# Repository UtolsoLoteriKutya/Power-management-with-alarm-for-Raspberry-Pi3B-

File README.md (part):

<html xmlns:v="urn:schemas-microsoft-com:vml"
xmlns:o="urn:schemas-microsoft-com:office:office"
xmlns:w="urn:schemas-microsoft-com:office:word"
xmlns:m="http://schemas.microsoft.com/office/2004/12/omml"
xmlns="http://www.w3.org/TR/REC-html40">

<head>
<meta http-equiv=Content-Type content="text/html; charset=windows-1250">
<meta name=ProgId content=Word.Document>
<meta name=Generator content="Microsoft Word 15">
<meta name=Originator content="Microsoft Word 15">
<link rel=File-List href="index_elemei/filelist.xml">
<link rel=Edit-Time-Data href="index_elemei/editdata.mso">
<!--[if !mso]>

<![endif]--><!--[if gte mso 9]><xml>
 <o:DocumentProperties>
  <o:Author>Citrák János</o:Author>
  <o:LastAuthor>Citrák János</o:LastAuthor>
  <o:Revision>5</o:Revision>
  <o:Created>2022-07-11T07:24:00Z</o:Created>
  <o:LastSaved>2022-07-11T10:03:00Z</o:LastSaved>
  <o:Pages>1</o:Pages>
  <o:Words>778</o:Words>
  <o:Characters>4903</o:Characters>
  <o:Lines>40</o:Lines>
  <o:Paragraphs>11</o:Paragraphs>
  <o:CharactersWithSpaces>5670</o:CharactersWithSpaces>
  <o:Version>16.00</o:Version>
 </o:DocumentProperties>
 <o:OfficeDocumentSettings>
  <o:AllowPNG/>
 </o:OfficeDocumentSettings>
</xml><![endif]-->
<link rel=themeData href="index_elemei/themedata.thmx">
<link rel=colorSchemeMapping href="index_elemei/colorschememapping.xml">
<!--[if gte mso 9]><xml>
 <w:WordDocument>
  <w:Zoom>90</w:Zoom>
  <w:TrackMoves>false</w:TrackMoves>
  <w:TrackFormatting/>
  <w:HyphenationZone>21</w:HyphenationZone>
  <w:PunctuationKerning/>
  <w:ValidateAgainstSchemas/>
  <w:SaveIfXMLInvalid>false</w:SaveIfXMLInvalid>
  <w:IgnoreMixedContent>false</w:IgnoreMixedContent>
  <w:AlwaysShowPlaceholderText>false</w:AlwaysShowPlaceholderText>
  <w:DoNotPromoteQF/>
  <w:LidThemeOther>DE</w:LidThemeOther>
  <w:LidThemeAsian>X-NONE</w:LidThemeAsian>
  <w:LidThemeComplexScript>AR-SA</w:LidThemeComplexScript>
  <w:Compatibility>
   <w:BreakWrappedTables/>
   <w:SnapToGridInCell/>
   <w:WrapTextWithPunct/>
   <w:UseAsianBreakRules/>
   <w:DontGrowAutofit/>
   <w:SplitPgBreakAndParaMark/>
   <w:EnableOpenTypeKerning/>
   <w:DontFlipMirrorIndents/>
   <w:OverrideTableStyleHps/>
  </w:Compatibility>
  <m:mathPr>
   <m:mathFont m:val="Cambria Math"/>
   <m:brkBin m:val="before"/>
   <m:brkBinSub m:val="&#45;-"/>
   <m:smallFrac m:val="off"/>
   <m:dispDef/>
   <m:lMargin m:val="0"/>
   <m:rMargin m:val="0"/>
   <m:defJc m:val="centerGroup"/>
   <m:wrapIndent m:val="1440"/>
   <m:intLim m:val="subSup"/>
   <m:naryLim m:val="undOvr"/>
  </m:mathPr></w:WordDocument>
</xml><![endif]--><!--[if gte mso 9]><xml>
 <w:LatentStyles DefLockedState="false" DefUnhideWhenUsed="false"
  DefSemiHidden="false" DefQFormat="false" DefPriority="99"
  LatentStyleCount="376">
  <w:LsdException Locked="false" Priority="0" QFormat="true" Name="Normal"/>
  <w:LsdException Locked="false" Priority="9" QFormat="true" Name="heading 1"/>
  <w:LsdException Locked="false" Priority="9" SemiHidden="true"
   UnhideWhenUsed="true" QFormat="true" Name="heading 2"/>
  <w:LsdException Locked="false" Priority="9" SemiHidden="true"
   UnhideWhenUsed="true" QFormat="true" Name="heading 3"/>
  <w:LsdException Locked="false" Priority="9" SemiHidden="true"
   UnhideWhenUsed="true" QFormat="true" Name="heading 4"/>
  <w:LsdException Locked="false" Priority="9" SemiHidden="true"
   UnhideWhenUsed="true" QFormat="true" Name="heading 5"/>
  <w:LsdException Locked="false" Priority="9" SemiHidden="true"
   UnhideWhenUsed="true" QFormat="true" Name="heading 6"/>
  <w:LsdException Locked="false" Priority="9" SemiHidden="true"
   UnhideWhenUsed="true" QFormat="true" Name="heading 7"/>
  <w:LsdException Locked="false" Priority="9" SemiHidden="true"
   UnhideWhenUsed="true" QFormat="true" Name="heading 8"/>
  <w:LsdException Locked="false" Priority="9" SemiHidden="true"
   UnhideWhenUsed="true" QFormat="true" Name="heading 9"/>
  <w:LsdException Locked="false" SemiHidden="true" UnhideWhenUsed="true"
   Name="index 1"/>
  <w:LsdException Locked="false" SemiHidden="true" UnhideWhenUsed="true"
   Name="index 2"/>
  <w:LsdException Locked="false" SemiHidden="true" UnhideWhenUsed="true"
   Name="index 3"/>
  <w:LsdException Locked="false" SemiHidden="true" UnhideWhenUsed="true"
   Name="index 4"/>
  <w:LsdException Locked="false" SemiHidden="true" UnhideWhenUsed="true"
   Name="index 5"/>
  <w:LsdException Locked="false" SemiHidden="true" UnhideWhenUsed="true"
   Name="index 6"/>
  <w:LsdException Locked="false" SemiHidden="true" UnhideWhenUsed="true"
   Name="index 7"/>
  <w:LsdException Locked="false" SemiHidden="true" UnhideWhenUsed="true"
   Name="index 8"/>
  <w:LsdException Locked="false" SemiHidden="true" UnhideWhenUsed="true"
   Name="index 9"/>
  <w:LsdException Locked="false" Priority="39" SemiHidden="true"
   UnhideWhenUsed="true" Name="toc 1"/>
  <w:LsdException Locked="false" Priority="39" SemiHidden="true"
   UnhideWhenUsed="true" Name="toc 2"/>
  <w:LsdException Locked="false" Priority="39" SemiHidden="true"
   UnhideWhenUsed="true" Name="toc 3"/>
  <w:LsdException Locked="false" Priority="39" SemiHidden="true"
   UnhideWhenUsed="true" Name="toc 4"/>
  <w:LsdException Locked="false" Priority="39" SemiHidden="true"
   UnhideWhenUsed="true" Name="toc 5"/>
  <w:LsdException Locked="false" Priority="39" SemiHidden="true"
   UnhideWhenUsed="true" Name="toc 6"/>
  <w:LsdException Locked="false" Priority="39" SemiHidden="true"
   UnhideWhenUsed="true" Name="toc 7"/>
  <w:LsdException Locked="false" Priority="39" SemiHidden="true"
   UnhideWhenUsed="true" Name="toc 8"/>
  <w:LsdException Locked="false" Priority="39" SemiHidden="true"
   UnhideWhenUsed="true" Name="toc 9"/>
  <w:LsdException Locked="false" SemiHidden="true" UnhideWhenUsed="true"
   Name="Normal Indent"/>
  <w:LsdException Locked="false" SemiHidden="true" UnhideWhenUsed="true"
   Name="footnote text"/>
  <w:LsdException Locked="false" SemiHidden="true" UnhideWhenUsed="true"
   Name="annotation text"/>
  <w:LsdException Locked="false" SemiHidden="true" UnhideWhenUsed="true"
   Name="header"/>
  <w:LsdException Locked="false" SemiHidden="true" UnhideWhenUsed="true"
   Name="footer"/>
  <w:LsdException Locked="false" SemiHidden="true" UnhideWhenUsed="true"
   Name="index heading"/>
  <w:LsdException Locked="false" Priority="35" SemiHidden="true"
   UnhideWhenUsed="true" QFormat="true" Name="caption"/>
  <w:LsdException Locked="false" SemiHidden="true" UnhideWhenUsed="true"
   Name="table of figures"/>
  <w:LsdException Locked="false" SemiHidden="true" UnhideWhenUsed="true"
   Name="envelope address"/>
  <w:LsdException Locked="false" SemiHidden="true" UnhideWhenUsed="true"
   Name="envelope return"/>
  <w:LsdException Locked="false" SemiHidden="true" UnhideWhenUsed="true"
   Name="footnote reference"/>
  <w:LsdException Locked="false" SemiHidden="true" UnhideWhenUsed="true"
   Name="annotation reference"/>
  <w:LsdException Locked="false" SemiHidden="true" UnhideWhenUsed="true"
   Name="line number"/>
  <w:LsdException Locked="false" SemiHidden="true" UnhideWhenUsed="true"
   Name="page number"/>
  <w:LsdException Locked="false" SemiHidden="true" UnhideWhenUsed="true"
   Name="endnote reference"/>
  <w:LsdException Locked="false" SemiHidden="true" UnhideWhenUsed="true"
   Name="endnote text"/>
  <w:LsdException Locked="false" SemiHidden="true" UnhideWhenUsed="true"
   Name="table of authorities"/>
  <w:LsdException Locked="false" SemiHidden="true" UnhideWhenUsed="true"
   Name="macro"/>
  <w:LsdException Locked="false" SemiHidden="true" UnhideWhenUsed="true"
   Name="toa heading"/>
  <w:LsdException Locked="false" SemiHidden="true" UnhideWhenUsed="true"
   Name="List"/>
  <w:LsdException Locked="false" SemiHidden="true" UnhideWhenUsed="true"
   Name="List Bullet"/>
  <w:LsdException Locked="false" SemiHidden="true" UnhideWhenUsed="true"
   Name="List Number"/>
  <w:LsdException Locked="false" SemiHidden="true" UnhideWhenUsed="true"
   Name="List 2"/>
  <w:LsdException Locked="false" SemiHidden="true" UnhideWhenUsed="true"
   Name="List 3"/>
  <w:LsdException Locked="false" SemiHidden="true" UnhideWhenUsed="true"
   Name="List 4"/>
  <w:LsdException Locked="false" SemiHidden="true" UnhideWhenUsed="true"
   Name="List 5"/>
  <w:LsdException Locked="false" SemiHidden="true" UnhideWhenUsed="true"
   Name="List Bullet 2"/>
  <w:LsdException Locked="false" SemiHidden="true" UnhideWhenUsed="true"
   Name="List Bullet 3"/>
  <w:LsdException Locked="false" SemiHidden="true" UnhideWhenUsed="true"
   Name="List Bullet 4"/>
  <w:LsdException Locked="false" SemiHidden="true" UnhideWhenUsed="true"
   Name="List Bullet 5"/>
  <w:LsdException Locked="false" SemiHidden="true" UnhideWhenUsed="true"
   Name="List Number 2"/>
  <w:LsdException Locked="false" SemiHidden="true" UnhideWhenUsed="true"
   Name="List Number 3"/>
  <w:LsdException Locked="false" SemiHidden="true" UnhideWhenUsed="true"
   Name="List Number 4"/>
  <w:LsdException Locked="false" SemiHidden="true" UnhideWhenUsed="true"
   Name="List Number 5"/>
  <w:LsdException Locked="false" Priority="10" QFormat="true" Name="Title"/>
  <w:LsdException Locked="false" SemiHidden="true" UnhideWhenUsed="true"
   Name="Closing"/>
  <w:LsdException Locked="false" SemiHidden="true" UnhideWhenUsed="true"
   Name="Signature"/>
  <w:LsdException Locked="false" Priority="1" SemiHidden="true"
   UnhideWhenUsed="true" Name="Default Paragraph Font"/>
  <w:LsdException Locked="false" SemiHidden="true" UnhideWhenUsed="true"
   Name="Body Text"/>
  <w:LsdException Locked="false" SemiHidden="true" UnhideWhenUsed="true"
   Name="Body Text Indent"/>
  <w:LsdException Locked="false" SemiHidden="true" UnhideWhenUsed="true"
   Name="List Continue"/>
  <w:LsdException Locked="false" SemiHidden="true" UnhideWhenUsed="true"
   Name="List Continue 2"/>
  <w:LsdException Locked="false" SemiHidden="true" UnhideWhenUsed="true"
   Name="List Continue 3"/>
  <w:LsdException Locked="false" SemiHidden="true" UnhideWhenUsed="true"
   Name="List Continue 4"/>
  <w:LsdException Locked="false" SemiHidden="true" UnhideWhenUsed="true"
   Name="List Continue 5"/>
  <w:LsdException Locked="false" SemiHidden="true" UnhideWhenUsed="true"
   Name="Message Header"/>
  <w:LsdException Locked="false" Priority="11" QFormat="true" Name="Subtitle"/>
  <w:LsdException Locked="false" SemiHidden="true" UnhideWhenUsed="true"
   Name="Salutation"/>
  <w:LsdException Locked="false" SemiHidden="true" UnhideWhenUsed="true"
   Name="Date"/>
  <w:LsdException Locked="false" SemiHidden="true" UnhideWhenUsed="true"
   Name="Body Text First Indent"/>
  <w:LsdException Locked="false" SemiHidden="true" UnhideWhenUsed="true"
   Name="Body Text First Indent 2"/>
  <w:LsdException Locked="false" SemiHidden="true" UnhideWhenUsed="true"
   Name="Note Heading"/>
  <w:LsdException Locked="false" SemiHidden="true" UnhideWhenUsed="true"
   Name="Body Text 2"/>
  <w:LsdException Locked="false" SemiHidden="true" UnhideWhenUsed="true"
   Name="Body Text 3"/>
  <w:LsdException Locked="false" SemiHidden="true" UnhideWhenUsed="true"
   Name="Body Text Indent 2"/>
  <w:LsdException Locked="false" SemiHidden="true" UnhideWhenUsed="true"
   Name="Body Text Indent 3"/>
  <w:LsdException Locked="false" SemiHidden="true" UnhideWhenUsed="true"
   Name="Block Text"/>
  <w:LsdException Locked="false" SemiHidden="true" UnhideWhenUsed="true"
   Name="Hyperlink"/>
  <w:LsdException Locked="false" SemiHidden="true" UnhideWhenUsed="true"
   Name="FollowedHyperlink"/>
  <w:LsdException Locked="false" Priority="22" QFormat="true" Name="Strong"/>
  <w:LsdException Locked="false" Priority="20" QFormat="true" Name="Emphasis"/>
  <w:LsdException Locked="false" SemiHidden="true" UnhideWhenUsed="true"
   Name="Document Map"/>
  <w:LsdException Locked="false" SemiHidden="true" UnhideWhenUsed="true"
   Name="Plain Text"/>
  <w:LsdException Locked="false" SemiHidden="true" UnhideWhenUsed="true"
   Name="E-mail Signature"/>
  <w:LsdException Locked="false" SemiHidden="true" UnhideWhenUsed="true"
   Name="HTML Top of Form"/>
  <w:LsdException Locked="false" SemiHidden="true" UnhideWhenUsed="true"
   Name="HTML Bottom of Form"/>
  <w:LsdException Locked="false" SemiHidden="true" UnhideWhenUsed="true"
   Name="Normal (Web)"/>
  <w:LsdException Locked="false" SemiHidden="true" UnhideWhenUsed="true"
   Name="HTML Acronym"/>
  <w:LsdException Locked="false" SemiHidden="true" UnhideWhenUsed="true"
   Name="HTML Address"/>
  <w:LsdException Locked="false" SemiHidden="true" UnhideWhenUsed="true"
   Name="HTML Cite"/>
  <w:LsdException Locked="false" SemiHidden="true" UnhideWhenUsed="true"
   Name="HTML Code"/>
  <w:LsdException Locked="false" SemiHidden="true" UnhideWhenUsed="true"
   Name="HTML Definition"/>
  <w:LsdException Locked="false" SemiHidden="true" UnhideWhenUsed="true"
   Name="HTML Keyboard"/>
  <w:LsdException Locked="false" SemiHidden="true" UnhideWhenUsed="true"
   Name="HTML Preformatted"/>
  <w:LsdException Locked="false" SemiHidden="true" UnhideWhenUsed="true"
   Name="HTML Sample"/>
  <w:LsdException Locked="false" SemiHidden="true" UnhideWhenUsed="true"
   Name="HTML Typewriter"/>
  <w:LsdException Locked="false" SemiHidden="true" UnhideWhenUsed="true"
   Name="HTML Variable"/>
  <w:LsdException Locked="false" SemiHidden="true" UnhideWhenUsed="true"
   Name="Normal Table"/>
  <w:LsdException Locked="false" SemiHidden="true" UnhideWhenUsed="true"
   Name="annotation subject"/>
  <w:LsdException Locked="false" SemiHidden="true" UnhideWhenUsed="true"
   Name="No List"/>
  <w:LsdException Locked="false" SemiHidden="true" UnhideWhenUsed="true"
   Name="Outline List 1"/>
  <w:LsdException Locked="false" SemiHidden="true" UnhideWhenUsed="true"
   Name="Outline List 2"/>
  <w:LsdException Locked="false" SemiHidden="true" UnhideWhenUsed="true"
   Name="Outline List 3"/>
  <w:LsdException Locked="false" SemiHidden="true" UnhideWhenUsed="true"
   Name="Table Simple 1"/>
  <w:LsdException Locked="false" SemiHidden="true" UnhideWhenUsed="true"
   Name="Table Simple 2"/>
  <w:LsdException Locked="false" SemiHidden="true" UnhideWhenUsed="true"
   Name="Table Simple 3"/>
  <w:LsdException Locked="false" SemiHidden="true" UnhideWhenUsed="true"
   Name="Table Classic 1"/>
  <w:LsdException Locked="false" SemiHidden="true" UnhideWhenUsed="true"
   Name="Table Classic 2"/>
  <w:LsdException Locked="false" SemiHidden="true" UnhideWhenUsed="true"
   Name="Table Classic 3"/>
  <w:LsdException Locked="false" SemiHidden="true" UnhideWhenUsed="true"
   Name="Table Classic 4"/>
  <w:LsdException Locked="false" SemiHidden="true" UnhideWhenUsed="true"
   Name="Table Colorful 1"/>
  <w:LsdException Locked="false" SemiHidden="true" UnhideWhenUsed="true"
   Name="Table Colorful 2"/>
  <w:LsdException Locked="false" SemiHidden="true" UnhideWhenUsed="true"
   Name="Table Colorful 3"/>
  <w:LsdException Locked="false" SemiHidden="true" UnhideWhenUsed="true"
   Name="Table Columns 1"/>
  <w:LsdException Locked="false" SemiHidden="true" UnhideWhenUsed="true"
   Name="Table Columns 2"/>
  <w:LsdException Locked="false" SemiHidden="true" UnhideWhenUsed="true"
   Name="Table Columns 3"/>
  <w:LsdException Locked="false" SemiHidden="true" UnhideWhenUsed="true"
   Name="Table Columns 4"/>
  <w:LsdException Locked="false" SemiHidden="true" UnhideWhenUsed="true"
   Name="Table Columns 5"/>
  <w:LsdException Locked="false" SemiHidden="true" UnhideWhenUsed="true"
   Name="Table Grid 1"/>
  <w:LsdException Locked="false" SemiHidden="true" UnhideWhenUsed="true"
   Name="Table Grid 2"/>
  <w:LsdException Locked="false" SemiHidden="true" UnhideWhenUsed="true"
   Name="Table Grid 3"/>
  <w:LsdException Locked="false" SemiHidden="true" UnhideWhenUsed="true"
   Name="Table Grid 4"/>
  <w:LsdException Locked="false" SemiHidden="true" UnhideWhenUsed="true"
   Name="Table Grid 5"/>
  <w:LsdException Locked="false" SemiHidden="true" UnhideWhenUsed="true"
   Name="Table Grid 6"/>
  <w:LsdException Locked="false" SemiHidden="true" UnhideWhenUsed="true"
   Name="Table Grid 7"/>
  <w:LsdException Locked="false" SemiHidden="true" UnhideWhenUsed="true"
   Name="Table Grid 8"/>
  <w:LsdException Locked="false" SemiHidden="true" UnhideWhenUsed="true"
   Name="Table List 1"/>
  <w:LsdException Locked="false" SemiHidden="true" UnhideWhenUsed="true"
   Name="Table List 2"/>
  <w:LsdException Locked="false" SemiHidden="true" UnhideWhenUsed="true"
   Name="Table List 3"/>
  <w:LsdException Locked="false" SemiHidden="true" UnhideWhenUsed="true"
   Name="Table List 4"/>
  <w:LsdException Locked="false" SemiHidden="true" UnhideWhenUsed="true"
   Name="Table List 5"/>
  <w:LsdException Locked="false" SemiHidden="true" UnhideWhenUsed="true"
   Name="Table List 6"/>
  <w:LsdException Locked="false" SemiHidden="true" UnhideWhenUsed="true"
   Name="Table List 7"/>
  <w:LsdException Locked="false" SemiHidden="true" UnhideWhenUsed="true"
   Name="Table List 8"/>
  <w:LsdException Locked="false" SemiHidden="true" UnhideWhenUsed="true"
   Name="Table 3D effects 1"/>
  <w:LsdException Locked="false" SemiHidden="true" UnhideWhenUsed="true"
   Name="Table 3D effects 2"/>
  <w:LsdException Locked="false" SemiHidden="true" UnhideWhenUsed="true"
   Name="Table 3D effects 3"/>
  <w:LsdException Locked="false" SemiHidden="true" UnhideWhenUsed="true"
   Name="Table Contemporary"/>
  <w:LsdException Locked="false" SemiHidden="true" UnhideWhenUsed="true"
   Name="Table Elegant"/>
  <w:LsdException Locked="false" SemiHidden="true" UnhideWhenUsed="true"
   Name="Table Professional"/>
  <w:LsdException Locked="false" SemiHidden="true" UnhideWhenUsed="true"
   Name="Table Subtle 1"/>
  <w:LsdException Locked="false" SemiHidden="true" UnhideWhenUsed="true"
   Name="Table Subtle 2"/>
  <w:LsdException Locked="false" SemiHidden="true" UnhideWhenUsed="true"
   Name="Table Web 1"/>
  <w:LsdException Locked="false" SemiHidden="true" UnhideWhenUsed="true"
   Name="Table Web 2"/>
  <w:LsdException Locked="false" SemiHidden="true" UnhideWhenUsed="true"
   Name="Table Web 3"/>
  <w:LsdException Locked="false" SemiHidden="true" UnhideWhenUsed="true"
   Name="Balloon Text"/>
  <w:LsdException Locked="false" Priority="39" Name="Table Grid"/>
  <w:LsdException Locked="false" SemiHidden="true" UnhideWhenUsed="true"
   Name="Table Theme"/>
  <w:LsdException Locked="false" SemiHidden="true" Name="Placeholder Text"/>
  <w:LsdException Locked="false" Priority="1" QFormat="true" Name="No Spacing"/>
  <w:LsdException Locked="false" Priority="60" Name="Light Shading"/>
  <w:LsdException Locked="false" Priority="61" Name="Light List"/>
  <w:LsdException Locked="false" Priority="62" Name="Light Grid"/>
  <w:LsdException Locked="false" Priority="63" Name="Medium Shading 1"/>
  <w:LsdException Locked="false" Priority="64" Name="Medium Shading 2"/>
  <w:LsdException Locked="false" Priority="65" Name="Medium List 1"/>
  <w:LsdException Locked="false" Priority="66" Name="Medium List 2"/>
  <w:LsdException Locked="false" Priority="67" Name="Medium Grid 1"/>
  <w:LsdException Locked="false" Priority="68" Name="Medium Grid 2"/>
  <w:LsdException Locked="false" Priority="69" Name="Medium Grid 3"/>
  <w:LsdException Locked="false" Priority="70" Name="Dark List"/>
  <w:LsdException Locked="false" Priority="71" Name="Colorful Shading"/>
  <w:LsdException Locked="false" Priority="72" Name="Colorful List"/>
  <w:LsdException Locked="false" Priority="73" Name="Colorful Grid"/>
  <w:LsdException Locked="false" Priority="60" Name="Light Shading Accent 1"/>
  <w:LsdException Locked="false" Priority="61" Name="Light List Accent 1"/>
  <w:LsdException Locked="false" Priority="62" Name="Light Grid Accent 1"/>
  <w:LsdException Locked="false" Priority="63" Name="Medium Shading 1 Accent 1"/>
  <w:LsdException Locked="false" Priority="64" Name="Medium Shading 2 Accent 1"/>
  <w:LsdException Locked="false" Priority="65" Name="Medium List 1 Accent 1"/>
  <w:LsdException Locked="false" SemiHidden="true" Name="Revision"/>
  <w:LsdException Locked="false" Priority="34" QFormat="true"
   Name="List Paragraph"/>
  <w:LsdException Locked="false" Priority="29" QFormat="true" Name="Quote"/>
  <w:LsdException Locked="false" Priority="30" QFormat="true"
   Name="Intense Quote"/>
  <w:LsdException Locked="false" Priority="66" Name="Medium List 2 Accent 1"/>
  <w:LsdException Locked="false" Priority="67" Name="Medium Grid 1 Accent 1"/>
  <w:LsdException Locked="false" Priority="68" Name="Medium Grid 2 Accent 1"/>
  <w:LsdException Locked="false" Priority="69" Name="Medium Grid 3 Accent 1"/>
  <w:LsdException Locked="false" Priority="70" Name="Dark List Accent 1"/>
  <w:LsdException Locked="false" Priority="71" Name="Colorful Shading Accent 1"/>
  <w:LsdException Locked="false" Priority="72" Name="Colorful List Accent 1"/>
  <w:LsdException Locked="false" Priority="73" Name="Colorful Grid Accent 1"/>
  <w:LsdException Locked="false" Priority="60" Name="Light Shading Accent 2"/>
  <w:LsdException Locked="false" Priority="61" Name="Light List Accent 2"/>
  <w:LsdException Locked="false" Priority="62" Name="Light Grid Accent 2"/>
  <w:LsdException Locked="false" Priority="63" Name="Medium Shading 1 Accent 2"/>
  <w:LsdException Locked="false" Priority="64" Name="Medium Shading 2 Accent 2"/>
  <w:LsdException Locked="false" Priority="65" Name="Medium List 1 Accent 2"/>
  <w:LsdException Locked="false" Priority="66" Name="Medium List 2 Accent 2"/>
  <w:LsdException Locked="false" Priority="67" Name="Medium Grid 1 Accent 2"/>
  <w:LsdException Locked="false" Priority="68" Name="Medium Grid 2 Accent 2"/>
  <w:LsdException Locked="false" Priority="69" Name="Medium Grid 3 Accent 2"/>
  <w:LsdException Locked="false" Priority="70" Name="Dark List Accent 2"/>
  <w:LsdException Locked="false" Priority="71" Name="Colorful Shading Accent 2"/>
  <w:LsdException Locked="false" Priority="72" Name="Colorful List Accent 2"/>
  <w:LsdException Locked="false" Priority="73" Name="Colorful Grid Accent 2"/>
  <w:LsdException Locked="false" Priority="60" Name="Light Shading Accent 3"/>
  <w:LsdException Locked="false" Priority="61" Name="Light List Accent 3"/>
  <w:LsdException Locked="false" Priority="62" Name="Light Grid Accent 3"/>
  <w:LsdException Locked="false" Priority="63" Name="Medium Shading 1 Accent 3"/>
  <w:LsdException Locked="false" Priority="64" Name="Medium Shading 2 Accent 3"/>
  <w:LsdException Locked="false" Priority="65" Name="Medium List 1 Accent 3"/>
  <w:LsdException Locked="false" Priority="66" Name="Medium List 2 Accent 3"/>
  <w:LsdException Locked="false" Priority="67" Name="Medium Grid 1 Accent 3"/>
  <w:LsdException Locked="false" Priority="68" Name="Medium Grid 2 Accent 3"/>
  <w:LsdException Locked="false" Priority="69" Name="Medium Grid 3 Accent 3"/>
  <w:LsdException Locked="false" Priority="70" Name="Dark List Accent 3"/>
  <w:LsdException Locked="false" Priority="71" Name="Colorful Shading Accent 3"/>
  <w:LsdException Locked="false" Priority="72" Name="Colorful List Accent 3"/>
  <w:LsdException Locked="false" Priority="73" Name="Colorful Grid Accent 3"/>
  <w:LsdException Locked="false" Priority="60" Name="Light Shading Accent 4"/>
  <w:LsdException Locked="false" Priority="61" Name="Light List Accent 4"/>
  <w:LsdException Locked="false" Priority="62" Name="Light Grid Accent 4"/>
  <w:LsdException Locked="false" Priority="63" Name="Medium Shading 1 Accent 4"/>
  <w:LsdException Locked="false" Priority="64" Name="Medium Shading 2 Accent 4"/>
  <w:LsdException Locked="false" Priority="65" Name="Medium List 1 Accent 4"/>
  <w:LsdException Locked="false" Priority="66" Name="Medium List 2 Accent 4"/>
  <w:LsdException Locked="false" Priority="67" Name="Medium Grid 1 Accent 4"/>
  <w:LsdException Locked="false" Priority="68" Name="Medium Grid 2 Accent 4"/>
  <w:LsdException Locked="false" Priority="69" Name="Medium Grid 3 Accent 4"/>
  <w:LsdException Locked="false" Priority="70" Name="Dark List Accent 4"/>
  <w:LsdException Locked="false" Priority="71" Name="Colorful Shading Accent 4"/>
  <w:LsdException Locked="false" Priority="72" Name="Colorful List Accent 4"/>
  <w:LsdException Locked="false" Priority="73" Name="Colorful Grid Accent 4"/>
  <w:LsdException Locked="false" Priority="60" Name="Light Shading Accent 5"/>
  <w:LsdException Locked="false" Priority="61" Name="Light List Accent 5"/>
  <w:LsdException Locked="false" Priority="62" Name="Light Grid Accent 5"/>
  <w:LsdException Locked="false" Priority="63" Name="Medium Shading 1 Accent 5"/>
  <w:LsdException Locked="false" Priority="64" Name="Medium Shading 2 Accent 5"/>
  <w:LsdException Locked="false" Priority="65" Name="Medium List 1 Accent 5"/>
  <w:LsdException Locked="false" Priority="66" Name="Medium List 2 Accent 5"/>
  <w:LsdException Locked="false" Priority="67" Name="Medium Grid 1 Accent 5"/>
  <w:LsdException Locked="false" Priority="68" Name="Medium Grid 2 Accent 5"/>
  <w:LsdException Locked="false" Priority="69" Name="Medium Grid 3 Accent 5"/>
  <w:LsdException Locked="false" Priority="70" Name="Dark List Accent 5"/>
  <w:LsdException Locked="false" Priority="71" Name="Colorful Shading Accent 5"/>
  <w:LsdException Locked="false" Priority="72" Name="Colorful List Accent 5"/>
  <w:LsdException Locked="false" Priority="73" Name="Colorful Grid Accent 5"/>
  <w:LsdException Locked="false" Priority="60" Name="Light Shading Accent 6"/>
  <w:LsdException Locked="false" Priority="61" Name="Light List Accent 6"/>
  <w:LsdException Locked="false" Priority="62" Name="Light Grid Accent 6"/>
  <w:LsdException Locked="false" Priority="63" Name="Medium Shading 1 Accent 6"/>
  <w:LsdException Locked="false" Priority="64" Name="Medium Shading 2 Accent 6"/>
  <w:LsdException Locked="false" Priority="65" Name="Medium List 1 Accent 6"/>
  <w:LsdException Locked="false" Priority="66" Name="Medium List 2 Accent 6"/>
  <w:LsdException Locked="false" Priority="67" Name="Medium Grid 1 Accent 6"/>
  <w:LsdException Locked="false" Priority="68" Name="Medium Grid 2 Accent 6"/>
  <w:LsdException Locked="false" Priority="69" Name="Medium Grid 3 Accent 6"/>
  <w:LsdException Locked="false" Priority="70" Name="Dark List Accent 6"/>
  <w:LsdException Locked="false" Priority="71" Name="Colorful Shading Accent 6"/>
  <w:LsdException Locked="false" Priority="72" Name="Colorful List Accent 6"/>
  <w:LsdException Locked="false" Priority="73" Name="Colorful Grid Accent 6"/>
  <w:LsdException Locked="false" Priority="19" QFormat="true"
   Name="Subtle Emphasis"/>
  <w:LsdException Locked="false" Priority="21" QFormat="true"
   Name="Intense Emphasis"/>
  <w:LsdException Locked="false" Priority="31" QFormat="true"
   Name="Subtle Reference"/>
  <w:LsdException Locked="false" Priority="32" QFormat="true"
   Name="Intense Reference"/>
  <w:LsdException Locked="false" Priority="33" QFormat="true" Name="Book Title"/>
  <w:LsdException Locked="false" Priority="37" SemiHidden="true"
   UnhideWhenUsed="true" Name="Bibliography"/>
  <w:LsdException Locked="false" Priority="39" SemiHidden="true"
   UnhideWhenUsed="true" QFormat="true" Name="TOC Heading"/>
  <w:LsdException Locked="false" Priority="41" Name="Plain Table 1"/>
  <w:LsdException Locked="false" Priority="42" Name="Plain Table 2"/>
  <w:LsdException Locked="false" Priority="43" Name="Plain Table 3"/>
  <w:LsdException Locked="false" Priority="44" Name="Plain Table 4"/>
  <w:LsdException Locked="false" Priority="45" Name="Plain Table 5"/>
  <w:LsdException Locked="false" Priority="40" Name="Grid Table Light"/>
  <w:LsdException Locked="false" Priority="46" Name="Grid Table 1 Light"/>
  <w:LsdException Locked="false" Priority="47" Name="Grid Table 2"/>
  <w:LsdException Locked="false" Priority="48" Name="Grid Table 3"/>
  <w:LsdException Locked="false" Priority="49" Name="Grid Table 4"/>
  <w:LsdException Locked="false" Priority="50" Name="Grid Table 5 Dark"/>
  <w:LsdException Locked="false" Priority="51" Name="Grid Table 6 Colorful"/>
  <w:LsdException Locked="false" Priority="52" Name="Grid Table 7 Colorful"/>
  <w:LsdException Locked="false" Priority="46"
   Name="Grid Table 1 Light Accent 1"/>
  <w:LsdException Locked="false" Priority="47" Name="Grid Table 2 Accent 1"/>
  <w:LsdException Locked="false" Priority="48" Name="Grid Table 3 Accent 1"/>
  <w:LsdException Locked="false" Priority="49" Name="Grid Table 4 Accent 1"/>
  <w:LsdException Locked="false" Priority="50" Name="Grid Table 5 Dark Accent 1"/>
  <w:LsdException Locked="false" Priority="51"
   Name="Grid Table 6 Colorful Accent 1"/>
  <w:LsdException Locked="false" Priority="52"
   Name="Grid Table 7 Colorful Accent 1"/>
  <w:LsdException Locked="false" Priority="46"
   Name="Grid Table 1 Light Accent 2"/>
  <w:LsdException Locked="false" Priority="47" Name="Grid Table 2 Accent 2"/>
  <w:LsdException Locked="false" Priority="48" Name="Grid Table 3 Accent 2"/>
  <w:LsdException Locked="false" Priority="49" Name="Grid Table 4 Accent 2"/>
  <w:LsdException Locked="false" Priority="50" Name="Grid Table 5 Dark Accent 2"/>
  <w:LsdException Locked="false" Priority="51"
   Name="Grid Table 6 Colorful Accent 2"/>
  <w:LsdException Locked="false" Priority="52"
   Name="Grid Table 7 Colorful Accent 2"/>
  <w:LsdException Locked="false" Priority="46"
   Name="Grid Table 1 Light Accent 3"/>
  <w:LsdException Locked="false" Priority="47" Name="Grid Table 2 Accent 3"/>
  <w:LsdException Locked="false" Priority="48" Name="Grid Table 3 Accent 3"/>
  <w:LsdException Locked="false" Priority="49" Name="Grid Table 4 Accent 3"/>
  <w:LsdException Locked="false" Priority="50" Name="Grid Table 5 Dark Accent 3"/>
  <w:LsdException Locked="false" Priority="51"
   Name="Grid Table 6 Colorful Accent 3"/>
  <w:LsdException Locked="false" Priority="52"
   Name="Grid Table 7 Colorful Accent 3"/>
  <w:LsdException Locked="false" Priority="46"
   Name="Grid Table 1 Light Accent 4"/>
  <w:LsdException Locked="false" Priority="47" Name="Grid Table 2 Accent 4"/>
  <w:LsdException Locked="false" Priority="48" Name="Grid Table 3 Accent 4"/>
  <w:LsdException Locked="false" Priority="49" Name="Grid Table 4 Accent 4"/>
  <w:LsdException Locked="false" Priority="50" Name="Grid Table 5 Dark Accent 4"/>
  <w:LsdException Locked="false" Priority="51"
   Name="Grid Table 6 Colorful Accent 4"/>
  <w:LsdException Locked="false" Priority="52"
   Name="Grid Table 7 Colorful Accent 4"/>
  <w:LsdException Locked="false" Priority="46"
   Name="Grid Table 1 Light Accent 5"/>
  <w:LsdException Locked="false" Priority="47" Name="Grid Table 2 Accent 5"/>
  <w:LsdException Locked="false" Priority="48" Name="Grid Table 3 Accent 5"/>
  <w:LsdException Locked="false" Priority="49" Name="Grid Table 4 Accent 5"/>
  <w:LsdException Locked="false" Priority="50" Name="Grid Table 5 Dark Accent 5"/>
  <w:LsdException Locked="false" Priority="51"
   Name="Grid Table 6 Colorful Accent 5"/>
  <w:LsdException Locked="false" Priority="52"
   Name="Grid Table 7 Colorful Accent 5"/>
  <w:LsdException Locked="false" Priority="46"
   Name="Grid Table 1 Light Accent 6"/>
  <w:LsdException Locked="false" Priority="47" Name="Grid Table 2 Accent 6"/>
  <w:LsdException Locked="false" Priority="48" Name="Grid Table 3 Accent 6"/>
  <w:LsdException Locked="false" Priority="49" Name="Grid Table 4 Accent 6"/>
  <w:LsdException Locked="false" Priority="50" Name="Grid Table 5 Dark Accent 6"/>
  <w:LsdException Locked="false" Priority="51"
   Name="Grid Table 6 Colorful Accent 6"/>
  <w:LsdException Locked="false" Priority="52"
   Name="Grid Table 7 Colorful Accent 6"/>
  <w:LsdException Locked="false" Priority="46" Name="List Table 1 Light"/>
  <w:LsdException Locked="false" Priority="47" Name="List Table 2"/>
  <w:LsdException Locked="false" Priority="48" Name="List Table 3"/>
  <w:LsdException Locked="false" Priority="49" Name="List Table 4"/>
  <w:LsdException Locked="false" Priority="50" Name="List Table 5 Dark"/>
  <w:LsdException Locked="false" Priority="51" Name="List Table 6 Colorful"/>
  <w:LsdException Locked="false" Priority="52" Name="List Table 7 Colorful"/>
  <w:LsdException Locked="false" Priority="46"
   Name="List Table 1 Light Accent 1"/>
  <w:LsdException Locked="false" Priority="47" Name="List Table 2 Accent 1"/>
  <w:LsdException Locked="false" Priority="48" Name="List Table 3 Accent 1"/>
  <w:LsdException Locked="false" Priority="49" Name="List Table 4 Accent 1"/>
  <w:LsdException Locked="false" Priority="50" Name="List Table 5 Dark Accent 1"/>
  <w:LsdException Locked="false" Priority="51"
   Name="List Table 6 Colorful Accent 1"/>
  <w:LsdException Locked="false" Priority="52"
   Name="List Table 7 Colorful Accent 1"/>
  <w:LsdException Locked="false" Priority="46"
   Name="List Table 1 Light Accent 2"/>
  <w:LsdException Locked="false" Priority="47" Name="List Table 2 Accent 2"/>
  <w:LsdException Locked="false" Priority="48" Name="List Table 3 Accent 2"/>
  <w:LsdException Locked="false" Priority="49" Name="List Table 4 Accent 2"/>
  <w:LsdException Locked="false" Priority="50" Name="List Table 5 Dark Accent 2"/>
  <w:LsdException Locked="false" Priority="51"
   Name="List Table 6 Colorful Accent 2"/>
  <w:LsdException Locked="false" Priority="52"
   Name="List Table 7 Colorful Accent 2"/>
  <w:LsdException Locked="false" Priority="46"
   Name="List Table 1 Light Accent 3"/>
  <w:LsdException Locked="false" Priority="47" Name="List Table 2 Accent 3"/>
  <w:LsdException Locked="false" Priority="48" Name="List Table 3 Accent 3"/>
  <w:LsdException Locked="false" Priority="49" Name="List Table 4 Accent 3"/>
  <w:LsdException Locked="false" Priority="50" Name="List Table 5 Dark Accent 3"/>
  <w:LsdException Locked="false" Priority="51"
   Name="List Table 6 Colorful Accent 3"/>
  <w:LsdException Locked="false" Priority="52"
   Name="List Table 7 Colorful Accent 3"/>
  <w:LsdException Locked="false" Priority="46"
   Name="List Table 1 Light Accent 4"/>
  <w:LsdException Locked="false" Priority="47" Name="List Table 2 Accent 4"/>
  <w:LsdException Locked="false" Priority="48" Name="List Table 3 Accent 4"/>
  <w:LsdException Locked="false" Priority="49" Name="List Table 4 Accent 4"/>
  <w:LsdException Locked="false" Priority="50" Name="List Table 5 Dark Accent 4"/>
  <w:LsdException Locked="false" Priority="51"
   Name="List Table 6 Colorful Accent 4"/>
  <w:LsdException Locked="false" Priority="52"
   Name="List Table 7 Colorful Accent 4"/>
  <w:LsdException Locked="false" Priority="46"
   Name="List Table 1 Light Accent 5"/>
  <w:LsdException Locked="false" Priority="47" Name="List Table 2 Accent 5"/>
  <w:LsdException Locked="false" Priority="48" Name="List Table 3 Accent 5"/>
  <w:LsdException Locked="false" Priority="49" Name="List Table 4 Accent 5"/>
  <w:LsdException Locked="false" Priority="50" Name="List Table 5 Dark Accent 5"/>
  <w:LsdException Locked="false" Priority="51"
   Name="List Table 6 Colorful Accent 5"/>
  <w:LsdException Locked="false" Priority="52"
   Name="List Table 7 Colorful Accent 5"/>
  <w:LsdException Locked="false" Priority="46"
   Name="List Table 1 Light Accent 6"/>
  <w:LsdException Locked="false" Priority="47" Name="List Table 2 Accent 6"/>
  <w:LsdException Locked="false" Priority="48" Name="List Table 3 Accent 6"/>
  <w:LsdException Locked="false" Priority="49" Name="List Table 4 Accent 6"/>
  <w:LsdException Locked="false" Priority="50" Name="List Table 5 Dark Accent 6"/>
  <w:LsdException Locked="false" Priority="51"
   Name="List Table 6 Colorful Accent 6"/>
  <w:LsdException Locked="false" Priority="52"
   Name="List Table 7 Colorful Accent 6"/>
  <w:LsdException Locked="false" SemiHidden="true" UnhideWhenUsed="true"
   Name="Mention"/>
  <w:LsdException Locked="false" SemiHidden="true" UnhideWhenUsed="true"
   Name="Smart Hyperlink"/>
  <w:LsdException Locked="false" SemiHidden="true" UnhideWhenUsed="true"
   Name="Hashtag"/>
  <w:LsdException Locked="false" SemiHidden="true" UnhideWhenUsed="true"
   Name="Unresolved Mention"/>
  <w:LsdException Locked="false" SemiHidden="true" UnhideWhenUsed="true"
   Name="Smart Link"/>
 </w:LatentStyles>
</xml><![endif]-->
<style>
<!--
 /* Font Definitions */
 @font-face
	{font-family:"Cambria Math";
	panose-1:2 4 5 3 5 4 6 3 2 4;
	mso-font-charset:238;
	mso-generic-font-family:roman;
	mso-font-pitch:variable;
	mso-font-signature:-536869121 1107305727 33554432 0 415 0;}
@font-face
	{font-family:Calibri;
	panose-1:2 15 5 2 2 2 4 3 2 4;
	mso-font-charset:238;
	mso-generic-font-family:swiss;
	mso-font-pitch:variable;
	mso-font-signature:-536859905 -1073732485 9 0 511 0;}
 /* Style Definitions */
 p.MsoNormal, li.MsoNormal, div.MsoNormal
	{mso-style-unhide:no;
	mso-style-qformat:yes;
	mso-style-parent:"";
	margin-top:0cm;
	margin-right:0cm;
	margin-bottom:8.0pt;
	margin-left:0cm;
	line-height:107%;
	mso-pagination:widow-orphan;
	font-size:11.0pt;
	font-family:"Calibri",sans-serif;
	mso-ascii-font-family:Calibri;
	mso-ascii-theme-font:minor-latin;
	mso-fareast-font-family:Calibri;
	mso-fareast-theme-font:minor-latin;
	mso-hansi-font-family:Calibri;
	mso-hansi-theme-font:minor-latin;
	mso-bidi-font-family:Arial;
	mso-bidi-theme-font:minor-bidi;
	mso-fareast-language:EN-US;}
a:link, span.MsoHyperlink
	{mso-style-priority:99;
	color:#0563C1;
	mso-themecolor:hyperlink;
	text-decoration:underline;
	text-underline:single;}
a:visited, span.MsoHyperlinkFollowed
	{mso-style-noshow:yes;
	mso-style-priority:99;
	color:#954F72;
	mso-themecolor:followedhyperlink;
	text-decoration:underline;
	text-underline:single;}
.MsoChpDefault
	{mso-style-type:export-only;
	mso-default-props:yes;
	font-family:"Calibri",sans-serif;
	mso-ascii-font-family:Calibri;
	mso-ascii-theme-font:minor-latin;
	mso-fareast-font-family:Calibri;
	mso-fareast-theme-font:minor-latin;
	mso-hansi-font-family:Calibri;
	mso-hansi-theme-font:minor-latin;
	mso-bidi-font-family:Arial;
	mso-bidi-theme-font:minor-bidi;
	mso-fareast-language:EN-US;}
.MsoPapDefault
	{mso-style-type:export-only;
	margin-bottom:8.0pt;
	line-height:107%;}
@page WordSection1
	{size:595.3pt 841.9pt;
	margin:70.85pt 70.85pt 2.0cm 70.85pt;
	mso-header-margin:35.4pt;
	mso-footer-margin:35.4pt;
	mso-paper-source:0;}
div.WordSection1
	{page:WordSection1;}
-->
</style>
<!--[if gte mso 10]>
<style>
 /* Style Definitions */
 table.MsoNormalTable
	{mso-style-name:"Normál táblázat";
	mso-tstyle-rowband-size:0;
	mso-tstyle-colband-size:0;
	mso-style-noshow:yes;
	mso-style-priority:99;
	mso-style-parent:"";
	mso-padding-alt:0cm 5.4pt 0cm 5.4pt;
	mso-para-margin-top:0cm;
	mso-para-margin-right:0cm;
	mso-para-margin-bottom:8.0pt;
	mso-para-margin-left:0cm;
	line-height:107%;
	mso-pagination:widow-orphan;
	font-size:11.0pt;
	font-family:"Calibri",sans-serif;
	mso-ascii-font-family:Calibri;
	mso-ascii-theme-font:minor-latin;
	mso-hansi-font-family:Calibri;
	mso-hansi-theme-font:minor-latin;
	mso-bidi-font-family:Arial;
	mso-bidi-theme-font:minor-bidi;
	mso-fareast-language:EN-US;}
</style>
<![endif]--><!--[if gte mso 9]><xml>
 <o:shapedefaults v:ext="edit" spidmax="1026"/>
</xml><![endif]--><!--[if gte mso 9]><xml>
 <o:shapelayout v:ext="edit">
  <o:idmap v:ext="edit" data="1"/>
 </o:shapelayout></xml><![endif]-->
</head>

<body lang=DE link="#0563C1" vlink="#954F72" style='tab-interval:35.4pt'>

<div class=WordSection1>

<p class=MsoNormal><b><span lang=EN-TT style='font-size:14.0pt;line-height:
107%;mso-ansi-language:EN-TT'><o:p>&nbsp;</o:p></span></b></p>

<p class=MsoNormal><b><span lang=EN-TT style='font-size:14.0pt;line-height:
107%;mso-ansi-language:EN-TT;mso-no-proof:yes'><!--[if gte vml 1]><v:shapetype
 id="_x0000_t75" coordsize="21600,21600" o:spt="75" o:preferrelative="t"
 path="m@4@5l@4@11@9@11@9@5xe" filled="f" stroked="f">
 <v:stroke joinstyle="miter"/>
 <v:formulas>
  <v:f eqn="if lineDrawn pixelLineWidth 0"/>
  <v:f eqn="sum @0 1 0"/>
  <v:f eqn="sum 0 0 @1"/>
  <v:f eqn="prod @2 1 2"/>
  <v:f eqn="prod @3 21600 pixelWidth"/>
  <v:f eqn="prod @3 21600 pixelHeight"/>
  <v:f eqn="sum @0 0 1"/>
  <v:f eqn="prod @6 1 2"/>
  <v:f eqn="prod @7 21600 pixelWidth"/>
  <v:f eqn="sum @8 21600 0"/>
  <v:f eqn="prod @7 21600 pixelHeight"/>
  <v:f eqn="sum @10 21600 0"/>
 </v:formulas>
 <v:path o:extrusionok="f" gradientshapeok="t" o:connecttype="rect"/>
 <o:lock v:ext="edit" aspectratio="t"/>
</v:shapetype><v:shape id="Kép_x0020_2" o:spid="_x0000_i1030" type="#_x0000_t75"
 alt="A képen szöveg, óra, idő, csatlakoztatott látható&#10;&#10;Automatikusan generált leírás"
 style='width:424.5pt;height:192.75pt;visibility:visible;mso-wrap-style:square'>
 <v:imagedata src="index_elemei/image001.jpg" o:title="A képen szöveg, óra, idő, csatlakoztatott látható&#10;&#10;Automatikusan generált leírás"/>
</v:shape><![endif]--><![if !vml]><![endif]><!--[if gte vml 1]><v:shape id="Kép_x0020_1"
 o:spid="_x0000_i1029" type="#_x0000_t75" alt="A képen szöveg látható&#10;&#10;Automatikusan generált leírás"
 style='width:342pt;height:192.75pt;rotation:180;visibility:visible;
 mso-wrap-style:square'>
 <v:imagedata src="index_elemei/image003.jpg" o:title="A képen szöveg látható&#10;&#10;Automatikusan generált leírás"/>
</v:shape><![endif]--><![if !vml]><![endif]></span></b><b><span
lang=EN-TT style='font-size:14.0pt;line-height:107%;mso-ansi-language:EN-TT'><o:p></o:p></span></b></p>

<p class=MsoNormal><b><span lang=EN-TT style='font-size:14.0pt;line-height:
107%;mso-ansi-language:EN-TT'><o:p>&nbsp;</o:p></span></b></p>

<p class=MsoNormal><b><span lang=EN-TT style='font-size:14.0pt;line-height:
107%;mso-ansi-language:EN-TT'>This page describes an extension to the new kind
of Raspberry Pi's to achieve &quot;PC-kind&quot; power management. The benefits
of it:</span></b><span lang=EN-TT style='font-size:14.0pt;line-height:107%;
mso-ansi-language:EN-TT'><o:p></o:p></span></p>

<p class=MsoNormal><span lang=EN-TT style='font-size:12.0pt;line-height:107%;
mso-ansi-language:EN-TT'><span style='mso-tab-count:1'>            </span>-<span
style='mso-tab-count:1'>           </span>Fully functioned power button<o:p></o:p></span></p>

<p class=MsoNormal><span lang=EN-TT style='font-size:12.0pt;line-height:107%;
mso-ansi-language:EN-TT'><span style='mso-tab-count:1'>            </span>-<span
style='mso-tab-count:1'>           </span>Achieving the board's low power
construction feature<o:p></o:p></span></p>

<p class=MsoNormal><span lang=EN-TT style='font-size:12.0pt;line-height:107%;
mso-ansi-language:EN-TT'><span style='mso-tab-count:1'>            </span>-<span
style='mso-tab-count:1'>           </span>additional RTC<span style='mso-tab-count:
1'> </span><o:p></o:p></span></p>

<p class=MsoNormal><span lang=EN-TT style='font-size:12.0pt;line-height:107%;
mso-ansi-language:EN-TT'><span style='mso-tab-count:1'>            </span>-<span
style='mso-tab-count:1'>           </span>programmable wake up<o:p></o:p></span></p>

<p class=MsoNormal><span lang=EN-TT style='font-size:12.0pt;line-height:107%;
mso-ansi-language:EN-TT'><o:p>&nbsp;</o:p></span></p>

<p class=MsoNormal><b><span lang=EN-TT style='font-size:12.0pt;line-height:
107%;mso-ansi-language:EN-TT'>Applicable boards as it is (tested):<o:p></o:p></span></b></p>

<p class=MsoNormal><span lang=EN-TT style='mso-ansi-language:EN-TT'><span
style='mso-tab-count:1'>                </span>-<span style='mso-tab-count:
1'>              </span>Raspberry Pi3 b+<o:p></o:p></span></p>

<p class=MsoNormal><span lang=EN-TT style='mso-ansi-language:EN-TT'><span
style='mso-tab-count:1'>                </span>-<span style='mso-tab-count:
1'>              </span>Raspberry Pi4<o:p></o:p></span></p>

<p class=MsoNormal><span lang=EN-TT style='mso-ansi-language:EN-TT'><o:p>&nbsp;</o:p></span></p>

<p class=MsoNormal><b><span lang=EN-TT style='font-size:12.0pt;line-height:
107%;mso-ansi-language:EN-TT'>Probably applicable with some modification (check
the description in the end of the page):<o:p></o:p></span></b></p>

<p class=MsoNormal><span lang=EN-TT style='mso-ansi-language:EN-TT'><span
style='mso-tab-count:1'>                </span>-<span style='mso-tab-count:
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
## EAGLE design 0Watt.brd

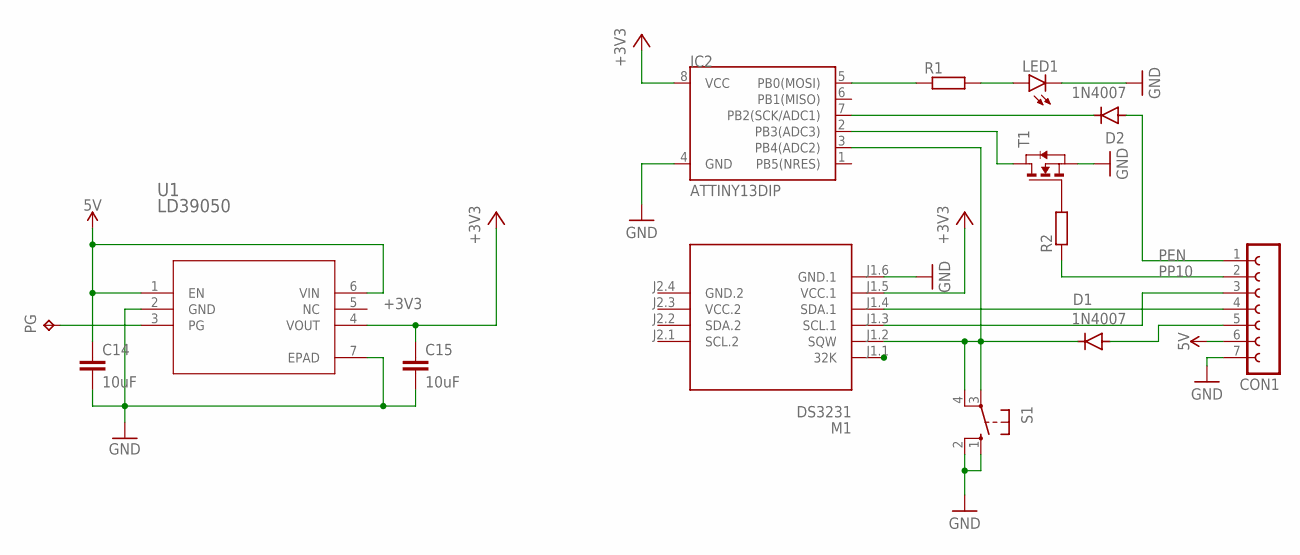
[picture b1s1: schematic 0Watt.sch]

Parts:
C14, C15: 10uF; C1206
CON1: FE07-1; FE07
D1, D2: 1N4007; DO-41
IC2: ATTINY13DIP; DIP08_MCU
LED1: LED5MM
M1: DS3231; RTC-DS3231-AT24C32
PG: TPB2,54; B2,54
R1: R-EU_0204/7; 0204/7
R2: R-EU_R0805; R0805
S1: 10-XX; B3F-10XX
T1: NMOSSOT23; SOT-23
U1: LD39050; DFN6_3X3_STM-M

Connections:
5V: C14.1, CON1.6, U1.1 (EN), U1.6 (VIN)
+3V3: C15.1, IC2.8 (VCC), M1.J1.5 (VCC.1), U1.4 (VOUT)
GND: C14.2, C15.2, CON1.7, IC2.4 (GND), LED1.K (C), M1.J1.6 (GND.1), S1.1 (S), S1.2 (S1), T1.2 (S), U1.2 (GND), U1.7 (EPAD)
GND.2: M1.J2.4 (GND.2)
GPIO24_: D1.C, IC2.3 (PB4(ADC2)), M1.J1.2 (SQW), S1.3, S1.4 (P1)
unnamed: D2.C, IC2.7 (PB2(SCK/ADC1))
unnamed: LED1.A, R1.2
unnamed: IC2.5 (PB0(MOSI)), R1.1
unnamed: R2.2, T1.3 (G)
unnamed: CON1.5, D1.A
unnamed: CON1.3, M1.J1.3 (SCL.1)
unnamed: CON1.4, M1.J1.4 (SDA.1)
unnamed: PG.TP, U1.3 (PG)
unnamed: IC2.2 (PB3(ADC3)), T1.1 (D)
PEN: CON1.1, D2.A
PP10: CON1.2, R2.1
VCC.2: M1.J2.3 (VCC.2)

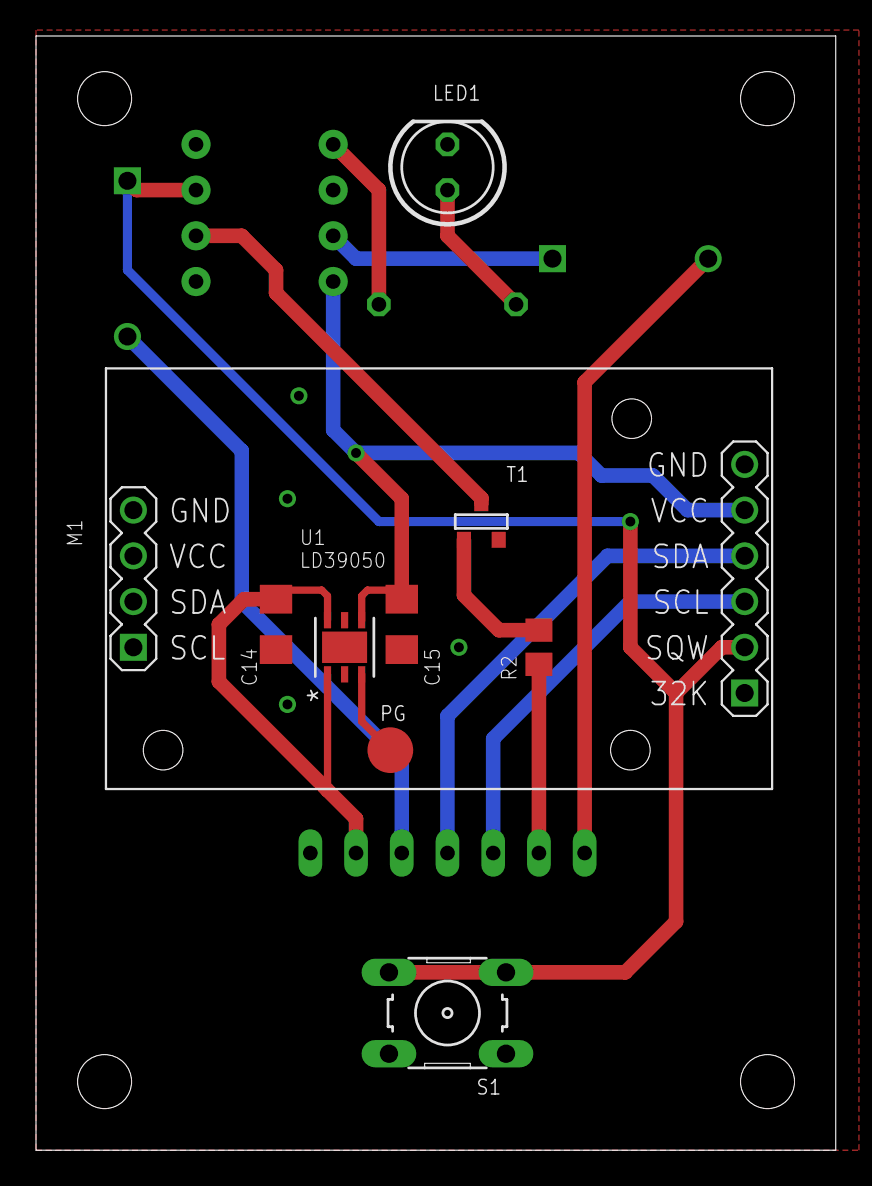
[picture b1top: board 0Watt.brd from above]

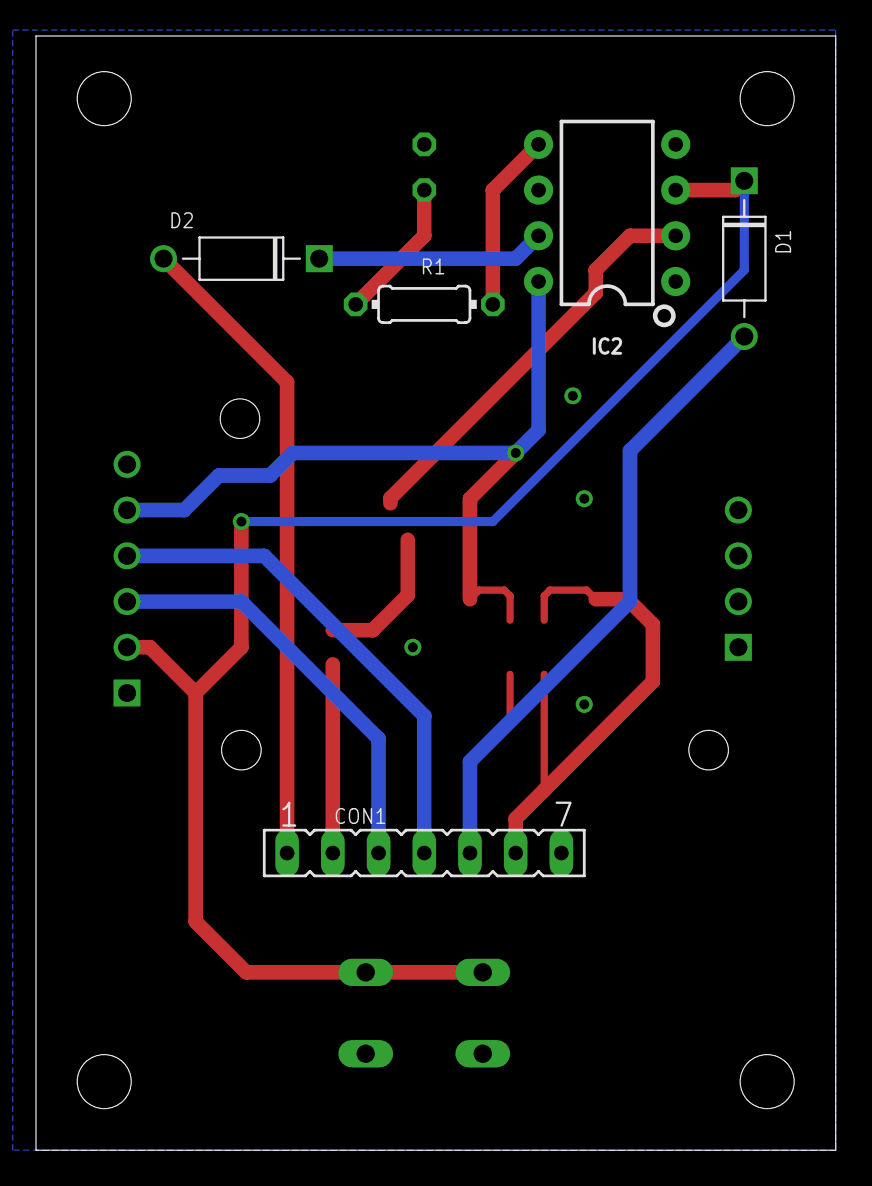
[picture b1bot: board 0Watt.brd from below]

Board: 2 copper layers, 44.4 x 61.9 mm, 14 parts (5 on the bottom side), 15 nets.

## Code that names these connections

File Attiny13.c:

/*
 * rpi_pm.c
 *
 * Created: 2022. 05. 09. 16:23:01
 * Author : huboiv
 */ 

#define TMR_PON		120000		// 120000 ~2mp
#define TMR_BOOTING	1800000		// 1800000 ~30mp
#define TMR_SHDN	1400000		// 1000000
#define TMR_PWROFF	40000

#define LED_PWM_MAX	200
#define LED_PWM_MIN	1

#define POWER_LED_IN	(1<<3) // PB3
#define ALARM_IN		(1<<4) // PB4
#define PEN_OUT			(1<<2) // PB2
#define LED1			(1<<1) // PB1
#define LED2			(1<<0) // PB0

#define POWER_LED_IN_DDR	DDRB
#define ALARM_IN_DDR		DDRB
#define PEN_OUT_DDR			DDRB

#define POWER_LED_IN_PORT	PORTB
#define ALARM_IN_PORT		PORTB
#define PEN_OUT_PORT		PORTB

#define POWER_LED_IN_PIN	PINB
#define ALARM_IN_PIN		PINB

#define LED1_DDR			DDRB
#define LED1_PORT			PORTB

#define LED2_DDR			DDRB
#define LED2_PORT			PORTB

#define isPowerLedIn	(POWER_LED_IN_PIN & POWER_LED_IN)
#define isAlarmIn		(ALARM_IN_PIN & ALARM_IN)

#define PenBe()	(PEN_OUT_PORT |= PEN_OUT)
#define Penki()	(PEN_OUT_PORT &= ~PEN_OUT)

#define Led1Be()	(LED1_PORT |= LED1)
#define Led1Ki()	(LED1_PORT &= ~LED1)

#define Led2Be()	(LED2_PORT |= LED2)
#define Led2Ki()	(LED2_PORT &= ~LED2)

#include <avr/io.h>
#include <avr/interrupt.h>

volatile uint8_t PowerLedFelfutoElDetektalva;
volatile uint8_t PowerLedLefutoElDetektalva;
volatile uint8_t AlarmLefutoElDetektalva;
// volatile uint8_t AlarmBemenetValtozas;
volatile uint8_t prevIsAlarmIn = 1;


#define PON_TMR		0	// Bekapcsolás után egy kis várakozás.
#define BOOTING		1	// Bootolás közben. Várjuk a Power LED alacsony szintet.
#define RUNNING		2	// Rendszer fut.
#define SHDN_TMR	3	// Leállítási folyamat közben, de lehet csak reboot.
#define STOP_TMR	4	// Rendszer leállítva és várunk egy kicsit PEN tiltásig.
#define POWER_OFF	5	// A rendszer továbbra is áll, PEN tiltás.

volatile uint8_t state = 0;

#define GYORS 3
#define LASSU 15

volatile uint8_t LedPwmDir	= 1;
volatile uint16_t IntDiv = 0;
volatile uint16_t IntSebesseg = LASSU;
volatile uint8_t IntVillogasEngedelyezes = 0;
volatile uint8_t IntLedPwm = 0;

volatile uint32_t tmrcnt;

void IoInit(void) {
	PEN_OUT_PORT |= PEN_OUT;				// Alapból magasszint, csak leállítás után alacsony indulásig.
	PEN_OUT_DDR |= PEN_OUT;
	LED1_DDR |= LED1;
	LED2_DDR |= LED2;
	POWER_LED_IN_DDR &= ~POWER_LED_IN;	// Bemenet.
	POWER_LED_IN_PORT |= POWER_LED_IN;	// Pull up.
	ALARM_IN_DDR &= ~ALARM_IN;
	ALARM_IN_PORT |= ALARM_IN;
	
	// MCUCR |= (1<<ISC01) | (1<<ISC01);	// Bármilyen logikai szintváltozásra INT0 megszakítás.
	GIMSK |= (0<<INT0) | (1<<PCIE);			// (INT0 nem) és PCIE engedélyezése.
	PCMSK |= (1<<PCINT3) | (1<<PCINT4);		// ALARM (PB3) bemenet változás megszakítás maszk.

	TCCR0A |= (1 << WGM01) | (1 << WGM00);
	TIMSK0 |= (1 << TOIE0);
	TCCR0B |= (1 << CS01) | (0 << CS00);
}

void LedPulsatingEnable(uint8_t value) {
	if(value) {
		OCR0A = value;
		} else {
		OCR0A = LED_PWM_MIN;
	}
	IntVillogasEngedelyezes = 1;
	TCCR0A |= (1 << COM0A1);
}

void LedPulsatingDisable(void) {
	IntVillogasEngedelyezes = 0;
	OCR0A = LED_PWM_MIN;
	TCCR0A &= ~(1 << COM0A1);
}

int main(void) {
    
	IoInit();

	PenBe();
	
	// Egy kis várakozás, mi lesz?
	PowerLedFelfutoElDetektalva = 0;
	PowerLedLefutoElDetektalva = 0;
	AlarmLefutoElDetektalva = 0;
	
	sei(); // Globális megszakítás engedélyezés.

	tmrcnt = TMR_PON;
	
	while (1) {
		switch(state) {
			case PON_TMR :
				PenBe();
				LedPulsatingDisable();
				tmrcnt--;
				if(tmrcnt == 0) { state = BOOTING; tmrcnt = TMR_BOOTING; }
				break;

			case BOOTING :
				LedPulsatingDisable();
				Led1Be();
				Led2Be();
				PenBe();
				tmrcnt--;			
				if(tmrcnt == 0) {
					state = RUNNING;
					PowerLedFelfutoElDetektalva = 0;
					PowerLedLefutoElDetektalva = 0;
				}
				break;

			case RUNNING :
				LedPulsatingDisable();
				PenBe();
				Led2Be();
				if(PowerLedFelfutoElDetektalva) {
					state = SHDN_TMR;
					tmrcnt=TMR_SHDN;
					PowerLedFelfutoElDetektalva = 0;
					PowerLedLefutoElDetektalva = 0;
				}
				break;

			case SHDN_TMR :
				LedPulsatingDisable();
				PenBe();
				tmrcnt--;
				if(tmrcnt == 0) { state = STOP_TMR; tmrcnt = TMR_PWROFF; }
				if(PowerLedLefutoElDetektalva) {
					state = RUNNING;
					PowerLedLefutoElDetektalva = 0;
					PowerLedFelfutoElDetektalva = 0;
					Led2Ki();
				}
				break;

			case STOP_TMR :
				PenBe();
				tmrcnt--;
				if(tmrcnt == 0) { state = POWER_OFF; AlarmLefutoElDetektalva = 0; LedPulsatingEnable(LED_PWM_MAX); }
				break;

			case POWER_OFF :
				Led1Ki();
				Penki();
				if(AlarmLefutoElDetektalva) { state = BOOTING; tmrcnt = TMR_BOOTING; AlarmLefutoElDetektalva = 0; }
				break;
		} // switch

    } // while
}

/*
// Power LED bemenet.
ISR(INT0_vect) {
	if(isPowerLedIn) {
		PowerLedLefutoElDetektalva = 0;
		PowerLedFelfutoElDetektalva = 1;
	} else {
		PowerLedFelfutoElDetektalva = 0;
		PowerLedLefutoElDetektalva = 1;
	}
}
*/

// Power LED, Alarm bemenet.
ISR(PCINT0_vect) {
	if(isAlarmIn && prevIsAlarmIn == 0) {	// Felfutó él.
		prevIsAlarmIn = 1;
		// AlarmLefutoElDetektalva = 1;
	}
	
	if(!isAlarmIn && prevIsAlarmIn == 1) {	// Lelfutó él.
		prevIsAlarmIn = 0;
		AlarmLefutoElDetektalva = 1;
	}

	if(!isPowerLedIn) {
		PowerLedLefutoElDetektalva = 0;
		PowerLedFelfutoElDetektalva = 1;
		} else {
		PowerLedFelfutoElDetektalva = 0;
		PowerLedLefutoElDetektalva = 1;
	}
}

// LED villogáshoz.
ISR(TIM0_OVF_vect) {
	if(IntVillogasEngedelyezes) {
		if(IntDiv == IntSebesseg) {
			IntDiv = 0;
			// Fenyero fokozas / csokkentes.
			OCR0A += LedPwmDir;
			// Iranyvaltas.
			if(OCR0A > LED_PWM_MAX || OCR0A < LED_PWM_MIN) LedPwmDir = -LedPwmDir;
		}
		IntDiv++;
	}
}

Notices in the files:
parts and their libraries:
diy-modules: Released under the Creative Commons Attribution 4.0 International License: http://creativecommons.org/licenses/by/4.0
SparkFun-Retired: Licensing: Creative Commons ShareAlike 4.0 International - https://creativecommons.org/licenses/by-sa/4.0
